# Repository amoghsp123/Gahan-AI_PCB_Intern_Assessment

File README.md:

# Gahan-AI PCB Intern Assessment

## Overview

This repository contains the submission for the PCB Designer Intern Assessment.

The project includes:

- STM32G431KBTx based PCB design
- USB Type-C interface
- SWD debugging connector
- I2C sensor interface
- UART sensor interface
- Status LED circuitry
- PCB layout, routing, and Gerber generation
- Reverse order of words program
- Embedded C LED blinking program

---

# STM32 USB Sensor Module PCB Design

## Features

- STM32G431KBTx Microcontroller
- USB Type-C USB 2.0 Connector
- SWD Debug Header
- I2C Interface Header
- UART Interface Header
- Status LED
- Decoupling Capacitors
- Pull-up Resistors
- Two-layer PCB Design

## Tools Used

- KiCad
- GitHub

### Note

Standard KiCad symbol libraries and footprint libraries were used for this project. No custom symbol or footprint libraries were created.

## Deliverables Included

- Schematic Design File
- PCB Layout File
- Gerber Files
- Drill Files
- Bill of Materials (BOM)

---

# Task 1 – Reverse Order of Words Program

## Objective

To develop a program that reverses the order of words in a given string.

## Features

- Accepts string input from the user
- Splits the sentence into words
- Reverses the order of words
- Displays the reversed sentence

## Language Used

- Python

## Sample Input

```text
C++ is powerful
```

## Sample Output

```text
powerful is C++
```

## Deliverables Included

- Source Code
- Code Comments and Explanation

---

# Task 3 – Embedded C LED Blinking Program

## Objective

To implement an Embedded C program for controlling LED blinking at different predefined speeds in a continuous cycle.

## Features

### Slow Speed Blinking
- 5 seconds ON
- 5 seconds OFF

### Medium Speed Blinking
- 2.5 seconds ON
- 2.5 seconds OFF

### Fast Speed Blinking
- 1 second ON
- 1 second OFF

### Speed Sequence
Slow → Medium → Fast → Repeat

- Each speed mode runs for two complete ON/OFF cycles before switching to the next mode.
- The process runs continuously until power-off.

## Tools Used

- Arduino IDE

## Deliverables Included

- Embedded C Source Code
- Code Comments and Explanation

---

# Repository Structure

```text
PCB_Design/
│
├── Schematic_Files/
├── PCB_Layout_Files/
├── Gerber_Files/
├── Drill_Files/
├── BOM/
└── Screenshots/

Task1/
│
├── reverse_words.py

Task3/
│
├── led_blink_speed_control.ino
└── README.md
```

---

# Author

Amogh Purohit

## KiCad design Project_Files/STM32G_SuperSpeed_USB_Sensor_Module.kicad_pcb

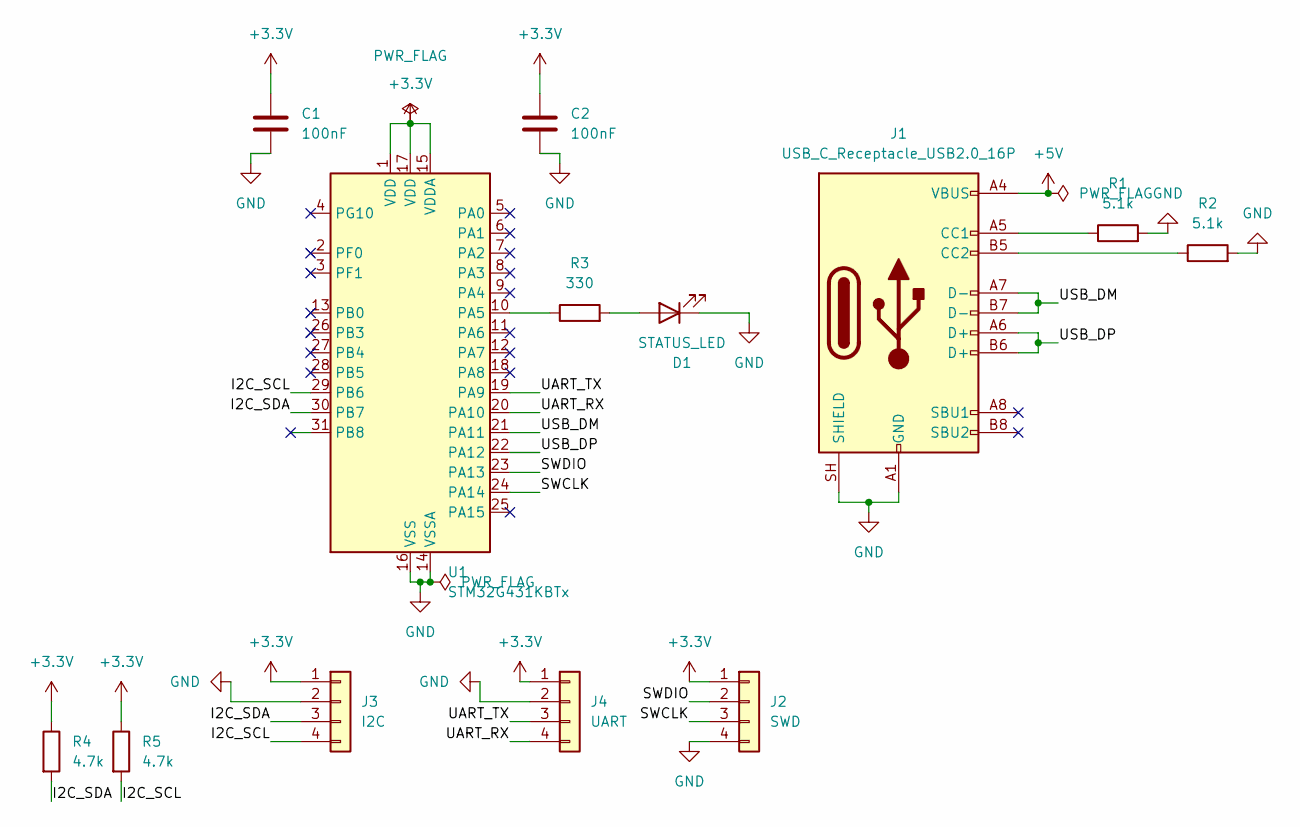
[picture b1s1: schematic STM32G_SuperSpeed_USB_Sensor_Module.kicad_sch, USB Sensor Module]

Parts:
C1, C2: 100nF; C_0805_2012Metric
D1: STATUS_LED; LED_0805_2012Metric
J1: USB_C_Receptacle_USB2.0_16P; USB_C_Receptacle_GCT_USB4085
J2: SWD; PinHeader_1x04_P2.54mm_Vertical
J3: I2C; PinHeader_1x04_P2.54mm_Vertical
J4: UART; PinHeader_1x04_P2.54mm_Vertical
R1, R2: 5.1k; R_0805_2012Metric
R3: 330; R_0805_2012Metric
R4, R5: 4.7k; R_0805_2012Metric
U1: STM32G431KBTx; LQFP-32_7x7mm_P0.8mm

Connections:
+3.3V: C1.1, C2.1, J2.1, J3.1, J4.1, R4.1, R5.1, U1.1 (VDD), U1.15 (VDDA), U1.17 (VDD)
+5V: J1.A4 (VBUS), J1.A9 (VBUS), J1.B4 (VBUS), J1.B9 (VBUS)
/I2C_SCL: J3.4, R5.2, U1.29 (PB6)
/I2C_SDA: J3.3, R4.2, U1.30 (PB7)
/SWCLK: J2.3, U1.24 (PA14)
/SWDIO: J2.2, U1.23 (PA13)
/UART_RX: J4.4, U1.20 (PA10)
/UART_TX: J4.3, U1.19 (PA9)
/USB_DM: J1.A7 (D-), J1.B7 (D-), U1.21 (PA11)
/USB_DP: J1.A6 (D+), J1.B6 (D+), U1.22 (PA12)
GND: C1.2, C2.2, D1.1 (K), J1.A1 (GND), J1.A12 (GND), J1.B1 (GND), J1.B12 (GND), J1.SH (SHIELD), J2.4, J3.2, J4.2, R1.2, R2.2, U1.14 (VSSA), U1.16 (VSS), U1.32 (VSS)
unnamed: D1.2 (A), R3.2
unnamed: J1.A5 (CC1), R1.1
unnamed: J1.B5 (CC2), R2.1
unnamed: R3.1, U1.10 (PA5)

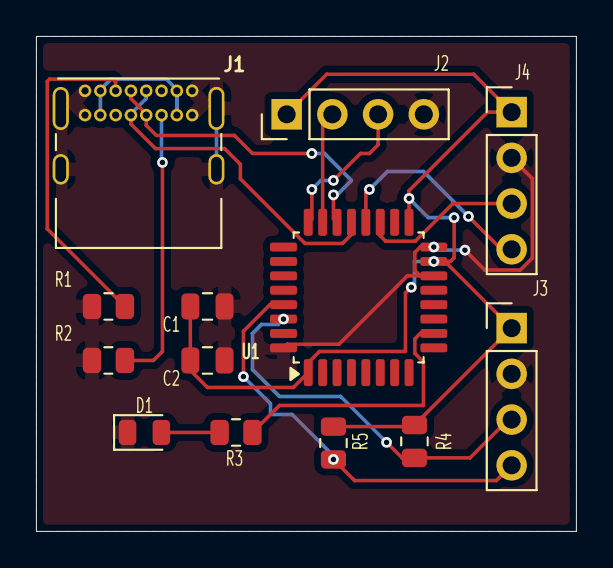
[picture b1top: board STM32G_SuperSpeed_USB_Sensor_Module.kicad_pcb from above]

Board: 2 copper layers, 30.0 x 27.5 mm, 13 parts (0 on the bottom side), 15 nets.

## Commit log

2026-05-11 README.md
2026-05-11 Create Project Files
2026-05-11 Create Gerber Files
2026-05-11 Create Images
2026-05-11 Create Documentation
2026-05-11 Cleaned repository structure
